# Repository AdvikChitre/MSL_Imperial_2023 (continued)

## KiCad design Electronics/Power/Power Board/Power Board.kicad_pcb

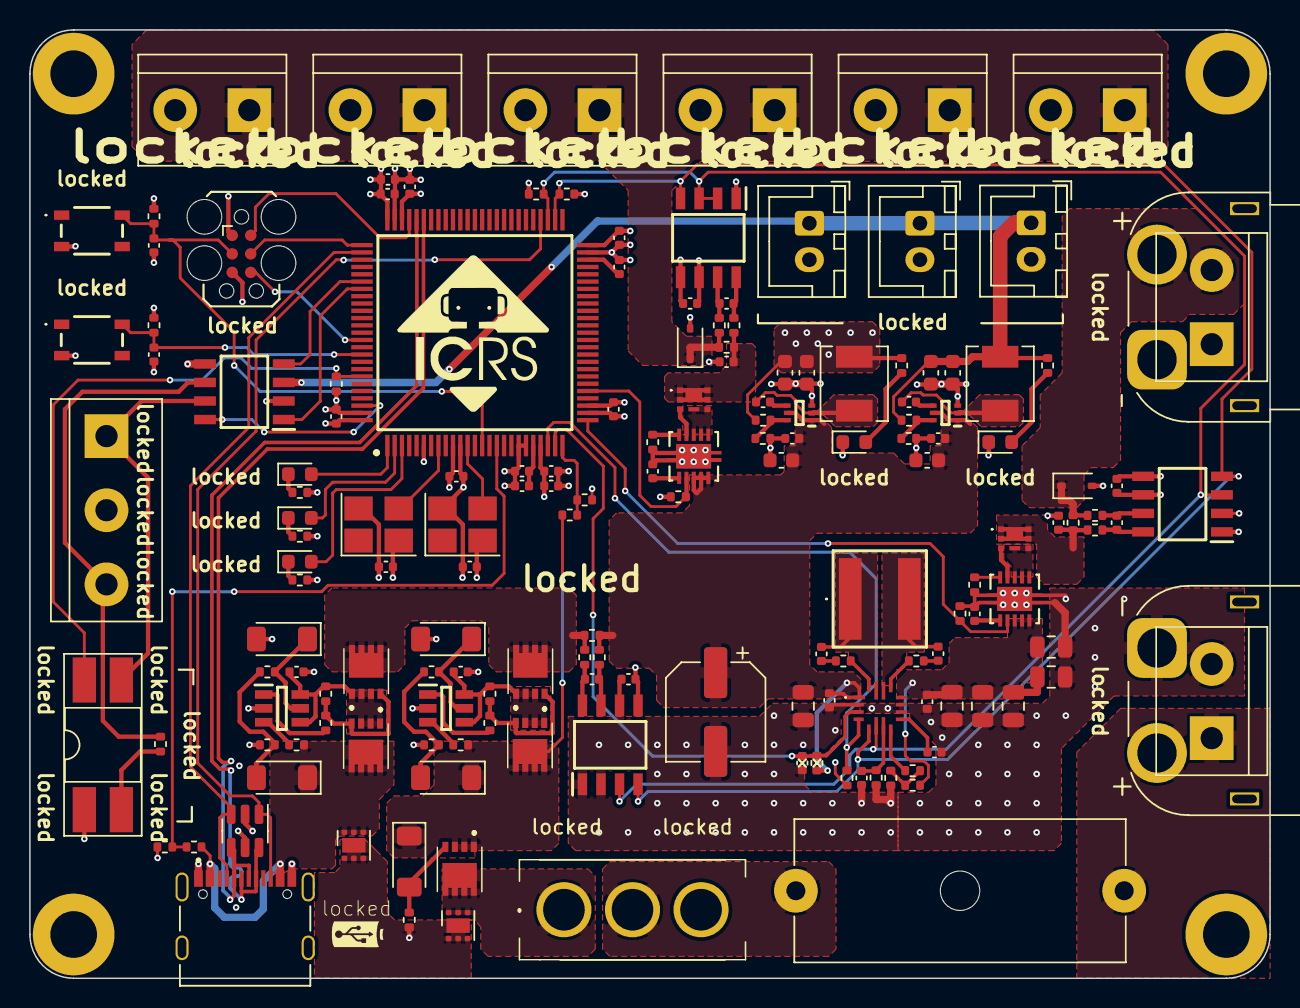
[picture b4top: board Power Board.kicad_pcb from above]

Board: 4 copper layers, 85.0 x 65.0 mm, 167 parts (0 on the bottom side), 94 nets.

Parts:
C201, C202, C205, C206, C209, C215, C216, C217, C218, C219, C220, C221, C235, C236, C301, C302, C305, C307, C310, C311, C312, C313, C314, C315: 100n; C_0402_1005Metric
C203, C211, C231, C237, C238, C306, C308: 1u; C_0402_1005Metric
C204, C233: 120p; C_0402_1005Metric
C207: 100u; CP_Elec_6.3x7.7
C208, C222, C223, C226, C227, C230: 22u; C_0805_2012Metric
C210, C212, C303, C304: 10n; C_0402_1005Metric
C213, C214, C224, C225, C228, C229: 22u; C_0603_1608Metric
C309: 4u7; C_0402_1005Metric
C316: 10u; C_0402_1005Metric
D201, D208: ZMM16V; D_MiniMELF
D202, D206: GREEN; LED_0603_1608Metric
D203, D209: ZMM4V7; D_MiniMELF
D204, D210: BAT760-115; D_SOD-323
D205: ZMM10V; D_MiniMELF
D301: Red; LED_0603_1608Metric
D302: Green; LED_0603_1608Metric
D303: Blue; LED_0603_1608Metric
F201: 10A; Fuseholder_Cylinder-5x20mm_Schurter_0031_8201_Horizontal_Op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
H101, H102, H103, H104: MountingHole_Pad; MountingHole_3.2mm_M3_DIN965_Pad
IC201, IC203, IC204: INA219AIDR; SOIC127P600X175-8N
IC202, IC208: TLV1805DBVR; SOT95P280X145-6N
IC205: MP28167GQ-A-Z; MP28167GQAZ
IC206, IC207: TPS563202DRLR; SOTFL50P160X60-6N
IC301: STM32U575VGT6; QFP50P1600X1600X160-100N
IC302: TJA1057GT/3; SOIC127P600X175-8N
J201: XT60PW-F; AMASS_XT60PW-F_1x02_P7.20mm_Horizontal
J202, J205, J206: JST-XH-2.50mm; JST_XH_B2B-XH-A_1x02_P2.50mm_Vertical
J203: XT60PW-M; AMASS_XT60PW-M_1x02_P7.20mm_Horizontal
J204, J215: Screw_Terminal_01x02; TerminalBlock_bornier-2_P5.08mm
J207, J208, J210, J211, J213, J214: Pluggable_Terminal_01x02; Pluggable_terminal-2_P5.08mm
J301: TC2030; Tag-Connect_TC2030-IDC-FP_2x03_P1.27mm_Vertical
J302: TYPE-C-31-M-12; HRO_TYPE-C-31-M-12
J303: Pluggable_Terminal_01x03; Pluggable_terminal-3_P5.08mm
L201: MPL-AL6050-4R7; MPLAL60504R7
L202: 4u7; L_Chilisin_BMRA00040420
L203: 3u3; L_Chilisin_BMRA00040420
Q201, Q202, Q203, Q204, Q205: DMP3013SFV-7; DMP3013SFV7
Q206, Q207: SSM6K513NU,LF; SSM6K513NULF
R201, R203, R211, R213, R215, R235, R236, R238: 22R; R_0402_1005Metric
R202, R214: 2m; R_0402_1005Metric
R204, R210, R231: 4k7; R_0402_1005Metric
R205, R212: 33k; R_0402_1005Metric
R206, R232, R311, R313: 1k; R_0402_1005Metric
R207, R208, R209, R217, R234: 100k; R_0402_1005Metric
R216, R225, R227, R230, R233, R302, R303, R304, R310, R312: 10k; R_0402_1005Metric
R218: 21k5; R_0402_1005Metric
R219: 787k; R_0402_1005Metric
R220, R221: 0R; R_0402_1005Metric
R222: 430k; R_0402_1005Metric
R223: 39k2; R_0402_1005Metric
R224: 52k; R_0402_1005Metric
R226: 31k; R_0402_1005Metric
R228, R305, R306: 2k2; R_0402_1005Metric
R229, R307, R308, R309: 1k5; R_0402_1005Metric
R237: 10m; R_0402_1005Metric
R301: 120R; R_0402_1005Metric
S301, S302: TS20-42-25-WT-160-SMT-TR; TS204225WT160SMTTRMSL
SW201: SW_SPDT; Toggle_switch
SW301: SW_DIP_x02; DIP-4_W8.89mm_SMDSocket_LongPads
U201: TCKE800NA_RF; WSON10B_TOS
U202: TCKE812NA_RF; WSON10B_TOS
U203, U303: TVS1800DRV; WSON-6-1EP_2x2mm_P0.65mm_EP1x1.6mm
U302: USBLC6-4SC6-ES; SOT-23-6
X301: 25MHz_Clock; Oscillator_SMD_Abracon_ASE-4Pin_3.2x2.5mm_HandSoldering
X302: 32.768kHz_Clock; Oscillator_SMD_Abracon_ASE-4Pin_3.2x2.5mm_HandSoldering

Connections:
12V_EN: C210.2, IC205.3 (EN), IC301.24 (PA1), R217.2
12V_OUT_EN: IC301.26 (PA3), R209.1, U202.2 (EN/UVLO)
+3.3V: C202.2, C206.2, C225.1, C229.1, C236.2, C301.1, C302.2, C307.1, C308.1, C310.1, C311.1, C312.1, C313.1, C314.1, C315.1, C316.1, IC201.2 (A0), IC201.5 (VS), IC203.5 (VS), IC204.5 (VS), IC301.6 (VBAT), IC301.11 (VDD_1), IC301.22 (VDDA), IC301.28 (VDD_2), IC301.50 (VDD_3), IC301.73 (VDDUSB), IC301.75 (VDD_4), IC301.100 (VDD_5), IC302.5 (VIO), J301.1 (VCC), L203.2, R216.1, R226.1, R229.1, R302.2, R303.2, R305.1, R306.1, SW301.1, U302.5 (VBUS), X301.4 (VDD), X302.4 (VDD)
+5V: C224.1, C228.1, IC302.3 (VCC), J202.1, J205.1, J206.1, L202.2, R224.1, R228.1
+12V: C221.1, C222.1, C223.1, C226.1, C227.1, C230.1, IC205.12 (OUT), R222.1, U202.3 (VIN), U202.4 (VIN), U202.5 (VIN)
/Control/CANH: IC302.7 (CANH), J303.1, SW301.3
/Control/CANL: IC302.6 (CANL), J303.3, R301.1
/Control/CAN_SW: R301.2, SW301.2
/Control/CC1: IC301.77 (PA15), J302.A5 (CC1), U302.3 (IO2)
/Control/CC2: IC301.54 (PB15), J302.B5 (CC2), U302.1 (IO1)
/Control/LEDB_K: D303.1 (K), R309.2
/Control/LEDG_K: D302.1 (K), R308.2
/Control/LEDR_K: D301.1 (K), R307.2
/Control/VCAP: C309.1, IC301.48 (VCAP)
/Control/VREF+: C305.1, C306.1, IC301.21 (VREF+)
/Power/3V3_BST: C220.1, IC207.4 (BST)
/Power/3V3_FB: IC207.6 (FB), R226.2, R227.1
/Power/3V3_LED_A: D206.2 (A), R229.2
/Power/3V3_SW: C220.2, IC207.2 (SW), L203.1
/Power/3V65: C211.2, IC205.9 (VCC)
/Power/5V_BST: C219.1, IC206.4 (BST)
/Power/5V_FB: IC206.6 (FB), R224.2, R225.1
/Power/5V_LED_A: D202.2 (A), R228.2
/Power/5V_SW: C219.2, IC206.2 (SW), L202.1
/Power/12V_FB: IC205.8 (FB), R219.1
/Power/12V_FB_MID: R219.2, R222.2, R223.1
/Power/12V_OUT: D204.1 (K), J201.2 (+), J215.2, R202.1, R203.1
/Power/12V_OUT_D: C237.1, Q207.1 (D), Q207.2 (D), Q207.5 (D), Q207.6 (D), Q207.7 (D), R201.1, R202.2
/Power/12V_OUT_DV/DT: C233.1, U202.1 (DV/DT)
/Power/12V_OUT_G: Q207.3 (G), U202.9 (EFET)
/Power/12V_OUT_ILIM: R212.1, U202.10 (ILIM)
/Power/12V_OUT_S: Q207.4 (S), Q207.8 (S), U202.6 (VOUT), U202.7 (VOUT), U202.8 (VOUT)
/Power/12V_SW1: C217.1, IC205.15 (SW1), L201.1
/Power/12V_SW2: C218.2, IC205.14 (SW2), L201.2
/Power/12V_VIN+: C201.1, IC201.8 (IN+), R201.2
/Power/12V_VIN-: C201.2, IC201.7 (IN-), R203.2
/Power/BST11: IC205.16 (BST1), R220.1
/Power/BST12: C217.2, R220.2
/Power/BST21: IC205.13 (BST2), R221.2
/Power/BST22: C218.1, R221.1
/Power/OC: C212.1, IC205.7 (OC), R218.1
/Power/RP_PMOS_G: D205.2 (A), Q205.4 (G), R210.1
/Power/VBAT_COMP-: IC202.3 (-), R230.2
/Power/VBAT_COMP_OUT: IC202.1, R211.1
/Power/VBAT_FUSED: F201.2, SW201.2 (B)
/Power/VBAT_GATE: Q201.4 (G), Q203.4 (G), R208.2, R211.2
/Power/VBAT_SHDN_A: D201.2 (A), R204.1, R206.1
/Power/VBAT_SHDN_K: D203.1 (K), IC202.5 (SH), R206.2
/Power/VBAT_SOURCE: C203.1, IC202.4 (+), IC202.6 (V+), Q201.1 (S_1), Q201.2 (S_2), Q201.3 (S_3), Q203.1 (S_1), Q203.2 (S_2), Q203.3 (S_3), R208.1
/Power/VBAT_SWITCHED: Q205.5 (D_1), Q205.6 (D_2), Q205.7 (D_3), Q205.8 (D_4), Q205.9 (D_5), SW201.1 (A), U203.4 (IN), U203.5 (IN), U203.6 (IN)
/Power/VBUS_COMP-: IC208.3 (-), R233.2
/Power/VBUS_COMP_OUT: IC208.1, R235.1
/Power/VBUS_GATE: Q202.4 (G), Q204.4 (G), R234.2, R235.2
/Power/VBUS_SHDN_A: D208.2 (A), R231.1, R232.1
/Power/VBUS_SHDN_K: D209.1 (K), IC208.5 (SH), R232.2
/Power/VBUS_SOURCE: C231.1, IC208.4 (+), IC208.6 (V+), Q202.1 (S_1), Q202.2 (S_2), Q202.3 (S_3), Q204.1 (S_1), Q204.2 (S_2), Q204.3 (S_3), R234.1
/Power/VDD_VIN+: C205.1, IC204.8 (IN+), R213.2
/Power/VDD_VIN-: C205.2, IC204.7 (IN-), R215.2
/Power/VOUT_D: C238.1, Q206.1 (D), Q206.2 (D), Q206.5 (D), Q206.6 (D), Q206.7 (D), R236.1, R237.2
/Power/VOUT_DV/DT: C204.1, U201.1 (DV/DT)
/Power/VOUT_G: Q206.3 (G), U201.9 (EFET)
/Power/VOUT_ILIM: R205.1, U201.10 (ILIM)
/Power/VOUT_S: Q206.4 (S), Q206.8 (S), U201.6 (VOUT), U201.7 (VOUT), U201.8 (VOUT)
/Power/VOUT_VIN+: C235.1, IC203.8 (IN+), R236.2
/Power/VOUT_VIN-: C235.2, IC203.7 (IN-), R238.2
ALT: IC205.4 (ALT), IC301.23 (PA0), R216.2
BOOT0: IC301.94 (PH3-BOOT0), R304.1, SW301.4
BTN: C303.1, IC301.91 (PB5), R302.1, S301.2 (NO_2)
CAN_RX: IC301.81 (PD0), IC302.4 (RXD)
CAN_TX: IC301.82 (PD1), IC302.1 (TXD)
GND: C202.1, C203.2, C204.2, C206.1, C207.2, C208.2, C209.1, C210.1, C211.1, C212.2, C213.2, C214.2, C215.2, C216.2, C221.2, C222.2, C223.2, C224.2, C225.2, C226.2, C227.2, C228.2, C229.2, C230.2, C231.2, C233.2, C236.1, C237.2, C238.2, C301.2, C302.1, C303.2, C304.2, C305.2, C306.2, C307.2, C308.2, C309.2, C310.2, C311.2, C312.2, C313.2, C314.2, C315.2, C316.2, D202.1 (K), D203.2 (A), D204.2 (A), D206.1 (K), D209.2 (A), D210.2 (A), IC201.1 (A1), IC201.6 (GND), IC202.2 (V-), IC203.1 (A1), IC203.6 (GND), IC204.1 (A1), IC204.2 (A0), IC204.6 (GND), IC205.2 (GND_1), IC205.10 (AGND), IC205.11 (GND_2), IC206.3 (GND), IC207.3 (GND), IC208.2 (V-), IC301.10 (VSS_1), IC301.19 (VSSA), IC301.20 (VREF-), IC301.27 (VSS_2), IC301.49 (VSS_3), IC301.74 (VSS_4), IC301.99 (VSS_5), IC302.2 (GND), J201.1 (-), J202.2, J203.1 (-), J204.2, J205.2, J206.2, J207.2, J208.2, J210.2, J211.2, J213.2, J214.2, J215.1, J301.5 (GND), J302.A1_B12 (GND), J302.B1_A12 (GND), J303.2, R204.2, R205.2, R207.2, R209.2, R210.2, R212.2, R218.2, R223.2, R225.2, R227.2, R231.2, R304.2, R307.1, R308.1, R309.1, R311.2, R313.2, S301.3 (COM_1), S302.3 (COM_1), U201.11 (GND), U202.11 (GND), U203.1 (GND), U203.2 (GND), U203.3 (GND), U203.7 (GND), U302.2 (GND), U303.1 (GND), U303.2 (GND), U303.3 (GND), U303.7 (GND), X301.2 (GND), X302.2 (GND)
LEDB: D303.2 (A), IC301.3 (PE4)
LEDG: D302.2 (A), IC301.1 (PE2)
LEDR: D301.2 (A), IC301.2 (PE3)
NRST: C304.1, IC301.14 (NRST), J301.3 (~RESET), R303.1, S302.2 (NO_2)
OSC25M: IC301.12 (PH0-OSC_IN), X301.3 (OUT)
OSC32K: IC301.8 (PC14-OSC32_IN), X302.3 (OUT)
SCL: IC201.4 (SCL), IC203.4 (SCL), IC204.4 (SCL), IC205.5 (SCL), IC301.52 (PB13), R305.2
SDA: IC201.3 (SDA), IC203.2 (A0), IC203.3 (SDA), IC204.3 (SDA), IC205.6 (SDA), IC301.53 (PB14), R306.2
SILENT: IC301.98 (PE1), IC302.8 (S)
SWCLK: IC301.76 (PA14), J301.4 (SWCLK)
SWDIO: IC301.72 (PA13), J301.2 (SWDIO)
SWO: IC301.89 (PB3), J301.6 (SWO)
USB_DN: IC301.70 (PA11), J302.A7 (DN1), J302.B7 (DN2), U302.4 (IO3)
USB_DP: IC301.71 (PA12), J302.A6 (DP1), J302.B6 (DP2), U302.6 (IO4)
VBAT: D201.1 (K), D205.1 (K), Q203.5 (D_1), Q203.6 (D_2), Q203.7 (D_3), Q203.8 (D_4), Q203.9 (D_5), Q205.1 (S_1), Q205.2 (S_2), Q205.3 (S_3), R230.1, R310.1
VBAT_RAW: F201.1, J203.2 (+), J204.1
VBAT/11: IC301.25 (PA2), R310.2, R311.1
VBUS: D208.1 (K), J302.A4_B9 (VBUS), J302.B4_A9 (VBUS), Q202.5 (D_1), Q202.6 (D_2), Q202.7 (D_3), Q202.8 (D_4), Q202.9 (D_5), R233.1, R312.1, U303.4 (IN), U303.5 (IN), U303.6 (IN)
VBUS/11: IC301.16 (PC1), R312.2, R313.1
VDD: C207.1, C208.1, C209.2, C213.1, C214.1, C215.1, C216.1, IC205.1 (IN), IC206.1 (VIN), IC206.5 (EN), IC207.1 (VIN), IC207.5 (EN), R214.1, R215.1, R217.1, U201.3 (VIN), U201.4 (VIN), U201.5 (VIN)
VIN: Q201.5 (D_1), Q201.6 (D_2), Q201.7 (D_3), Q201.8 (D_4), Q201.9 (D_5), Q204.5 (D_1), Q204.6 (D_2), Q204.7 (D_3), Q204.8 (D_4), Q204.9 (D_5), R213.1, R214.2
VOUT: D210.1 (K), J207.1, J208.1, J210.1, J211.1, J213.1, J214.1, R237.1, R238.1
VOUT_EN: IC301.30 (PA5), R207.1, U201.2 (EN/UVLO)

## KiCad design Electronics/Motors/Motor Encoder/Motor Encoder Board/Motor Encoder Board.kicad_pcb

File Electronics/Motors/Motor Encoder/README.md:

| Part | Function | Price/unit | Quantity | Link |
| - | - | - | - | - |
| AS5600-ASOT | Magnetic potentiometer | 0.98 | 1 | [LCSC](https://www.lcsc.com/product-detail/Position-Sensor_AMS-AS5600-ASOT_C499458.html)

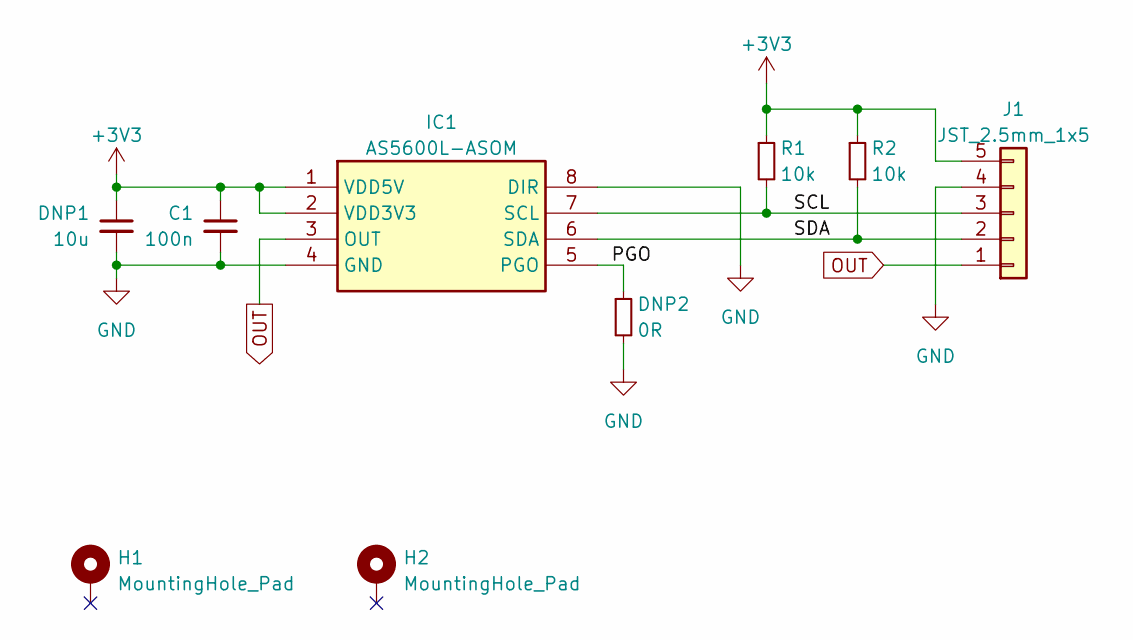
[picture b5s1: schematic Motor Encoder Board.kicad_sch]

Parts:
C1: 100n; C_0402_1005Metric
DNP1: 10u; C_0402_1005Metric
DNP2: 0R; R_0402_1005Metric
H1, H2: MountingHole_Pad; MountingHole_3.2mm_M3_DIN965_Pad
IC1: AS5600L-ASOM; SOIC127P600X175-8N; Mouser Part Number 985-AS5600L-ASOM
J1: JST_2.5mm_1x5; JST_XH_B5B-XH-A_1x05_P2.50mm_Vertical
R1, R2: 10k; R_0402_1005Metric

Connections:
+3V3: C1.1, DNP1.1, IC1.1 (VDD5V), IC1.2 (VDD3V3), J1.5, R1.1, R2.1
/PGO: DNP2.1, IC1.5 (PGO)
/SCL: IC1.7 (SCL), J1.3, R1.2
/SDA: IC1.6 (SDA), J1.2, R2.2
GND: C1.2, DNP1.2, DNP2.2, IC1.4 (GND), IC1.8 (DIR), J1.4
OUT: IC1.3 (OUT), J1.1

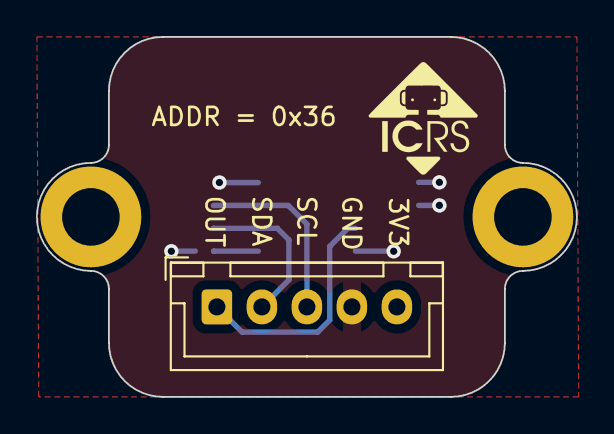
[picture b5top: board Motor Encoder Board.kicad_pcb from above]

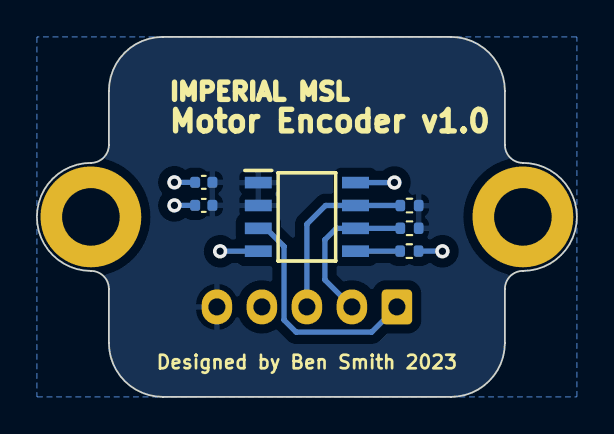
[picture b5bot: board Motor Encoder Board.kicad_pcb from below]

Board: 2 copper layers, 30.0 x 20.0 mm, 9 parts (6 on the bottom side), 6 nets.

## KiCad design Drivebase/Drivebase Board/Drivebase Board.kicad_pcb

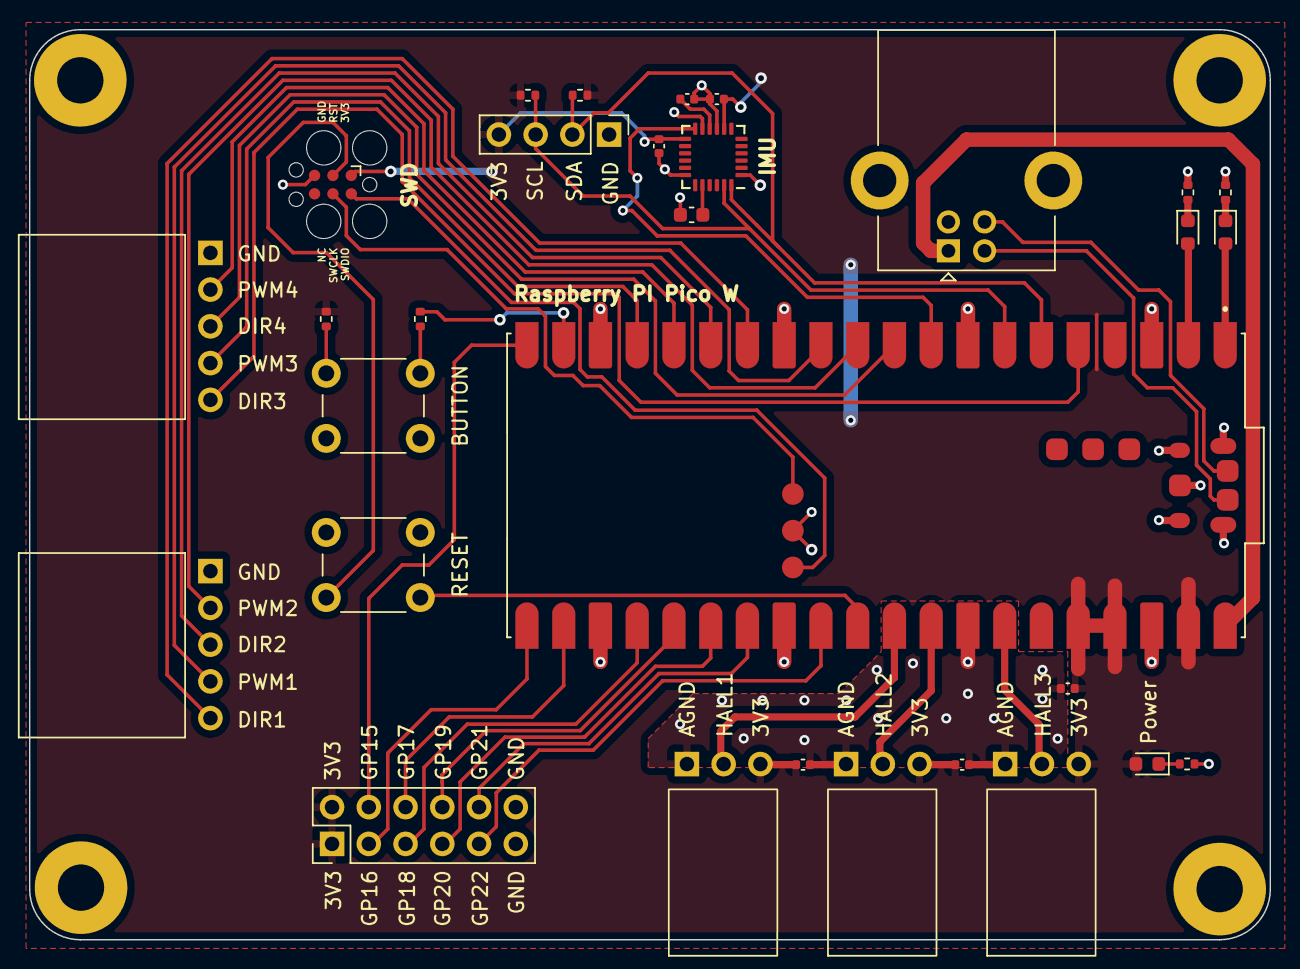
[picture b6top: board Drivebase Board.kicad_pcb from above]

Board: 2 copper layers, 85.8 x 62.9 mm, 37 parts (0 on the bottom side), 40 nets.

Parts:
C101, C102, C103, C104, C106: 100n; C_0402_1005Metric
C105: 2n2; C_0603_1608Metric
C107: 10n; C_0402_1005Metric
D101, D102, D103: LED_Small; LED_0603_1608Metric
H101, H102, H103, H104: MountingHole; MountingHole_3.2mm_M3_Pad
J101, J102: Conn_01x05_Male; 5pin right angle header
J103, J104, J105: Conn_01x03_Male; 3pin right angle header
J106: TC2030-IDC; Tag-Connect_TC2030-IDC-FP_2x03_P1.27mm_Vertical
J107: Conn_01x04_Male; PinHeader_1x04_P2.54mm_Vertical
J108: USB_A; USB_B_Lumberg_2411_02_Horizontal
J109: Conn_02x06_Odd_Even; PinHeader_2x06_P2.54mm_Vertical
R101, R102: 4k7; R_0402_1005Metric
R103, R105, R106, R107: 330R; R_0402_1005Metric
R104: 100k; R_0402_1005Metric
SW101, SW102: PSH_BTN; SW_PUSH_6mm_H5mm
TP101, TP102, TP103: TestPoint; TestPoint_Pad_D1.5mm
U101: SC0915; MODULE_SC0915
U102: MPU-6050; InvenSense_QFN-24_4x4mm_P0.5mm

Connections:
+3V3: C101.1, C102.1, C103.1, C106.1, C107.1, D101.2 (A), J103.3, J104.3, J105.3, J106.1, J107.4, J109.1, J109.2, R101.1, R102.1, R104.2, U101.36 (3V3_OUT), U101.37 (3V3_EN), U101.39 (VSYS), U102.8 (VDDIO), U102.13 (VDD)
/IMU_CPOUT: C105.1, U102.20 (CPOUT)
/IMU_REGOUT: C104.1, U102.10 (REGOUT)
/LED1_K: D102.1 (K), R106.1
/LED2_K: D103.1 (K), R107.1
/LED_PWR_K: D101.1 (K), R105.1
BTN: R103.2, U101.19 (GP14)
DIR1: J102.5, U101.14 (GP10)
DIR2: J102.3, U101.15 (GP11)
DIR3: J101.5, U101.5 (GP3)
DIR4: J101.3, U101.10 (GP7)
DM: J108.2 (D-), U101.TP2 (TP2_USB_DM)
DP: J108.3 (D+), U101.TP3 (TP3_USB_DP)
GND: C104.2, C105.2, C106.2, C107.2, J101.1, J102.1, J106.5, J107.1, J108.4 (GND), J108.5 (Shield), J109.11, J109.12, R105.2, R106.2, R107.2, SW101.1, SW102.2, TP103.1, U101.3 (GND), U101.8 (GND), U101.13 (GND), U101.18 (GND), U101.23 (GND), U101.28 (GND), U101.38 (GND), U101.A (USB_SHIELD), U101.B (USB_SHIELD), U101.C (USB_SHIELD), U101.D (USB_SHIELD), U101.TP1 (TP1_GND), U102.1 (CLKIN), U102.9 (AD0), U102.11 (FSYNC), U102.18 (GND)
GNDA: C101.2, C102.2, C103.2, J103.1, J104.1, J105.1, U101.33 (AGND)
GPIO15: J109.4, U101.20 (GP15)
GPIO16: J109.3, U101.21 (GP16)
GPIO17: J109.6, U101.22 (GP17)
GPIO18: J109.5, U101.24 (GP18)
GPIO19: J109.8, U101.25 (GP19)
GPIO20: J109.7, U101.26 (GP20)
GPIO21: J109.10, U101.27 (GP21)
GPIO22: J109.9, U101.29 (GP22)
HALL1: J103.2, U101.31 (GP26)
HALL2: J104.2, U101.32 (GP27)
HALL3: J105.2, U101.34 (GP28)
IMU_INT: U101.9 (GP6), U102.12 (INT)
LED1: D102.2 (A), U101.1 (GP0)
LED2: D103.2 (A), U101.2 (GP1)
unnamed: R103.1, R104.1, SW101.2
PWM1: J102.4, U101.12 (GP9)
PWM2: J102.2, U101.11 (GP8)
PWM3: J101.4, U101.17 (GP13)
PWM4: J101.2, U101.16 (GP12)
RST: J106.3, SW102.1, U101.30 (~RUN)
SCL: J107.3, R102.2, U101.7 (GP5), U102.23 (SCL)
SDA: J107.2, R101.2, U101.6 (GP4), U102.24 (SDA)
SWCLK: J106.4, TP101.1
SWDIO: J106.2, TP102.1
VBUS: J108.1 (VBUS), U101.40 (VBUS)

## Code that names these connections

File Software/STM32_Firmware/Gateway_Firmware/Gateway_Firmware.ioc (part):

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Mcu.Name=STM32H723ZGTx
Mcu.Package=LQFP144
Mcu.UserName=STM32H723ZGTx
PA1.Mode=RMII
PA1.Signal=ETH_REF_CLK
PA11.Mode=Device_Only_FS
PA11.Signal=USB_OTG_HS_DM
PA12.Mode=Device_Only_FS
PA12.Signal=USB_OTG_HS_DP
PA13(JTMS/SWDIO).Mode=Trace_Asynchronous_SW
PA13(JTMS/SWDIO).Signal=DEBUG_JTMS-SWDIO
PA14(JTCK/SWCLK).Mode=Trace_Asynchronous_SW
PA14(JTCK/SWCLK).Signal=DEBUG_JTCK-SWCLK
PA2.Mode=RMII
PA2.Signal=ETH_MDIO
PA7.Mode=RMII
PA7.Signal=ETH_CRS_DV
PA8.GPIOParameters=GPIO_Label
PA8.GPIO_Label=SDMMC1_CD
PA8.Signal=GPIO_Input
PB11.Mode=RMII
PB11.Signal=ETH_TX_EN
PB12.Mode=RMII
PB12.Signal=ETH_TXD0
PB13.Mode=RMII
PB13.Signal=ETH_TXD1
PB3(JTDO/TRACESWO).Mode=Trace_Asynchronous_SW
PB3(JTDO/TRACESWO).Signal=DEBUG_JTDO-SWO
PB5.Mode=FDCAN_Activate
PB5.Signal=FDCAN2_RX
PB6.Mode=FDCAN_Activate
PB6.Signal=FDCAN2_TX
PC1.Mode=RMII
PC1.Signal=ETH_MDC
PC10.Mode=SD_4_bits_Wide_bus
PC10.Signal=SDMMC1_D2
PC11.Mode=SD_4_bits_Wide_bus
PC11.Signal=SDMMC1_D3
PC12.Mode=SD_4_bits_Wide_bus
PC12.Signal=SDMMC1_CK
PC14-OSC32_IN.Mode=LSE-External-Clock-Source
PC14-OSC32_IN.Signal=RCC_OSC32_IN
PC4.Mode=RMII
PC4.Signal=ETH_RXD0
PC5.Mode=RMII
PC5.Signal=ETH_RXD1
PC8.Mode=SD_4_bits_Wide_bus
PC8.Signal=SDMMC1_D0
PC9.Mode=SD_4_bits_Wide_bus
PC9.Signal=SDMMC1_D1
PD0.Mode=FDCAN_Activate
PD0.Signal=FDCAN1_RX
PD1.Mode=FDCAN_Activate
PD1.Signal=FDCAN1_TX
PD2.Mode=SD_4_bits_Wide_bus
PD2.Signal=SDMMC1_CMD
PF6.Mode=FDCAN_Activate
PF6.Signal=FDCAN3_RX
PF7.Mode=FDCAN_Activate
PF7.Signal=FDCAN3_TX
PH0-OSC_IN.Mode=HSE-External-Clock-Source
PH0-OSC_IN.Signal=RCC_OSC_IN
RCC.SYSCLKFreq_VALUE=550000000
RCC.SYSCLKSource=RCC_SYSCLKSOURCE_PLLCLK
board=custom

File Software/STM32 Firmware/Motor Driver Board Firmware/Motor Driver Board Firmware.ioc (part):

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Mcu.Name=STM32H723ZGTx
Mcu.Package=LQFP144
Mcu.UserName=STM32H723ZGTx
PA0.Signal=S_TIM2_CH1_ETR
PA1.Signal=S_TIM2_CH2
PA11.Mode=Device_Only_FS
PA11.Signal=USB_OTG_HS_DM
PA12.Mode=Device_Only_FS
PA12.Signal=USB_OTG_HS_DP
PA13(JTMS/SWDIO).Mode=Trace_Asynchronous_SW
PA13(JTMS/SWDIO).Signal=DEBUG_JTMS-SWDIO
PA14(JTCK/SWCLK).Mode=Trace_Asynchronous_SW
PA14(JTCK/SWCLK).Signal=DEBUG_JTCK-SWCLK
PA4.Signal=COMP_DAC11_group
PA6.Signal=ADCx_INP3
PA8.Mode=I2C
PA8.Signal=I2C3_SCL
PB0.Signal=ADCx_INP9
PB10.Mode=I2C
PB10.Signal=I2C2_SCL
PB11.Mode=I2C
PB11.Signal=I2C2_SDA
PB12.Signal=GPIO_Input
PB13.Signal=GPIO_Input
PB14.Signal=S_TIM12_CH1
PB15.Signal=S_TIM12_CH2
PB3(JTDO/TRACESWO).Mode=Trace_Asynchronous_SW
PB3(JTDO/TRACESWO).Signal=DEBUG_JTDO-SWO
PC14-OSC32_IN.Mode=LSE-External-Clock-Source
PC14-OSC32_IN.Signal=RCC_OSC32_IN
PC9.Mode=I2C
PC9.Signal=I2C3_SDA
PD0.Mode=FDCAN_Activate
PD0.Signal=FDCAN1_RX
PD1.Mode=FDCAN_Activate
PD1.Signal=FDCAN1_TX
PD10.Signal=GPIO_Input
PD8.Signal=GPIO_Output
PD9.Signal=GPIO_Input
PE11.Signal=S_TIM1_CH2
PE12.Mode=Full_Duplex_Master
PE12.Signal=SPI4_SCK
PE13.Mode=Full_Duplex_Master
PE13.Signal=SPI4_MISO
PE14.Mode=Full_Duplex_Master
PE14.Signal=SPI4_MOSI
PE4.Mode=NSS_Signal_Hard_Output
PE4.Signal=SPI4_NSS
PE9.Signal=S_TIM1_CH1
PF11.Mode=IN2-Single-Ended
PF11.Signal=ADC1_INP2
PF14.Mode=I2C
PF14.Signal=I2C4_SCL
PF15.Mode=I2C
PF15.Signal=I2C4_SDA
PH0-OSC_IN.Mode=HSE-External-Clock-Source
PH0-OSC_IN.Signal=RCC_OSC_IN
RCC.SYSCLKFreq_VALUE=550000000
RCC.SYSCLKSource=RCC_SYSCLKSOURCE_PLLCLK
board=custom

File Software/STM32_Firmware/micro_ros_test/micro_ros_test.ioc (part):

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Mcu.Name=STM32H723ZGTx
Mcu.Package=LQFP144
Mcu.UserName=STM32H723ZGTx
PA1.GPIOParameters=GPIO_Speed,GPIO_PuPd,GPIO_Mode
PA1.GPIO_Mode=GPIO_MODE_AF_PP
PA1.GPIO_PuPd=GPIO_NOPULL
PA1.GPIO_Speed=GPIO_SPEED_FREQ_LOW
PA1.Mode=RMII
PA1.Signal=ETH_REF_CLK
PA10.GPIOParameters=GPIO_Label
PA10.GPIO_Label=USB_FS_ID
PA10.Mode=OTG/Dual-Role-Device-FS
PA10.Signal=USB_OTG_HS_ID
PA11.GPIOParameters=GPIO_Label
PA11.GPIO_Label=USB_FS_DM
PA11.Mode=OTG/Dual-Role-Device-FS
PA11.Signal=USB_OTG_HS_DM
PA12.GPIOParameters=GPIO_Label
PA12.GPIO_Label=USB_FS_DP
PA12.Mode=OTG/Dual-Role-Device-FS
PA12.Signal=USB_OTG_HS_DP
PA13(JTMS/SWDIO).GPIOParameters=GPIO_Label
PA13(JTMS/SWDIO).GPIO_Label=SWDIO
PA13(JTMS/SWDIO).Mode=Trace_Asynchronous_SW
PA13(JTMS/SWDIO).Signal=DEBUG_JTMS-SWDIO
PA14(JTCK/SWCLK).GPIOParameters=GPIO_Label
PA14(JTCK/SWCLK).GPIO_Label=SWCLK
PA14(JTCK/SWCLK).Mode=Trace_Asynchronous_SW
PA14(JTCK/SWCLK).Signal=DEBUG_JTCK-SWCLK
PA2.GPIOParameters=GPIO_Speed,GPIO_PuPd,GPIO_Mode
PA2.GPIO_Mode=GPIO_MODE_AF_PP
PA2.GPIO_PuPd=GPIO_NOPULL
PA2.GPIO_Speed=GPIO_SPEED_FREQ_LOW
PA2.Mode=RMII
PA2.Signal=ETH_MDIO
PA7.GPIOParameters=GPIO_Speed,GPIO_PuPd,GPIO_Mode
PA7.GPIO_Mode=GPIO_MODE_AF_PP
PA7.GPIO_PuPd=GPIO_NOPULL
PA7.GPIO_Speed=GPIO_SPEED_FREQ_LOW
PA7.Mode=RMII
PA7.Signal=ETH_CRS_DV
PA9.GPIOParameters=GPIO_Label
PA9.GPIO_Label=USB_FS_VBUS
PA9.Mode=Activate_VBUS_FS
PA9.Signal=USB_OTG_HS_VBUS
PB0.GPIOParameters=GPIO_Label
PB0.GPIO_Label=LED_GREEN
PB0.Signal=GPIO_Output
PB13.GPIOParameters=GPIO_Speed,GPIO_PuPd,GPIO_Mode
PB13.GPIO_Mode=GPIO_MODE_AF_PP
PB13.GPIO_PuPd=GPIO_NOPULL
PB13.GPIO_Speed=GPIO_SPEED_FREQ_LOW
PB13.Mode=RMII
PB13.Signal=ETH_TXD1
PB14.GPIOParameters=GPIO_Label
PB14.GPIO_Label=LED_RED
PB14.Signal=GPIO_Output
PB3(JTDO/TRACESWO).GPIOParameters=GPIO_Label
PB3(JTDO/TRACESWO).GPIO_Label=SWO
PB3(JTDO/TRACESWO).Mode=Trace_Asynchronous_SW
PB3(JTDO/TRACESWO).Signal=DEBUG_JTDO-SWO
PC1.GPIOParameters=GPIO_Speed,GPIO_PuPd,GPIO_Mode
PC1.GPIO_Mode=GPIO_MODE_AF_PP
PC1.GPIO_PuPd=GPIO_NOPULL
PC1.GPIO_Speed=GPIO_SPEED_FREQ_LOW
PC1.Mode=RMII
PC1.Signal=ETH_MDC
PC13.GPIOParameters=GPIO_Label
PC13.GPIO_Label=B1 (Blue_User_Button)
PC13.Signal=GPIO_Input
PC14-OSC32_IN.Mode=LSE-External-Oscillator
PC14-OSC32_IN.Signal=RCC_OSC32_IN
PC15-OSC32_OUT.Mode=LSE-External-Oscillator
PC15-OSC32_OUT.Signal=RCC_OSC32_OUT
PC4.GPIOParameters=GPIO_Speed,GPIO_PuPd,GPIO_Mode
PC4.GPIO_Mode=GPIO_MODE_AF_PP
PC4.GPIO_PuPd=GPIO_NOPULL
PC4.GPIO_Speed=GPIO_SPEED_FREQ_LOW
PC4.Mode=RMII
PC4.Signal=ETH_RXD0
PC5.GPIOParameters=GPIO_Speed,GPIO_PuPd,GPIO_Mode
PC5.GPIO_Mode=GPIO_MODE_AF_PP
PC5.GPIO_PuPd=GPIO_NOPULL
PC5.GPIO_Speed=GPIO_SPEED_FREQ_LOW
PC5.Mode=RMII
PC5.Signal=ETH_RXD1
PD10.GPIOParameters=GPIO_Label
PD10.GPIO_Label=USB_FS_PWR_EN
PD10.Signal=GPIO_Output
PD8.GPIOParameters=GPIO_Label
PD8.GPIO_Label=STLK_VCP_RX
PD8.Mode=Asynchronous
PD8.Signal=USART3_TX
PD9.GPIOParameters=GPIO_Label
PD9.GPIO_Label=STLK_VCP_TX
PD9.Mode=Asynchronous
PD9.Signal=USART3_RX
PE1.GPIOParameters=GPIO_Label
PE1.GPIO_Label=LED_YELLOW
PE1.Signal=GPIO_Output
PG11.GPIOParameters=GPIO_Speed,GPIO_PuPd,GPIO_Mode
PG11.GPIO_Mode=GPIO_MODE_AF_PP
PG11.GPIO_PuPd=GPIO_NOPULL
PG11.GPIO_Speed=GPIO_SPEED_FREQ_LOW
PG11.Mode=RMII
PG11.Signal=ETH_TX_EN
PG13.GPIOParameters=GPIO_Speed,GPIO_PuPd,GPIO_Mode
PG13.GPIO_Mode=GPIO_MODE_AF_PP
PG13.GPIO_PuPd=GPIO_NOPULL
PG13.GPIO_Speed=GPIO_SPEED_FREQ_LOW
PG13.Mode=RMII
PG13.Signal=ETH_TXD0
PG7.GPIOParameters=GPIO_Label
PG7.GPIO_Label=USB_FS_OVCR
PG7.Signal=GPXTI7
PH0-OSC_IN.GPIOParameters=GPIO_Label
PH0-OSC_IN.GPIO_Label=MCO
PH0-OSC_IN.Mode=HSE-External-Clock-Source
PH0-OSC_IN.Signal=RCC_OSC_IN
PH1-OSC_OUT.Signal=RCC_OSC_OUT
RCC.HSE_VALUE=8000000
RCC.SYSCLKFreq_VALUE=550000000
RCC.SYSCLKSource=RCC_SYSCLKSOURCE_PLLCLK
board=NUCLEO-H723ZG
boardIOC=true

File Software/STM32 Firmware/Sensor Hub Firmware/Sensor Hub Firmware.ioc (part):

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Mcu.Name=STM32H723ZGTx
Mcu.Package=LQFP144
Mcu.UserName=STM32H723ZGTx
PA11.Mode=Device_Only_FS
PA11.Signal=USB_OTG_HS_DM
PA12.Mode=Device_Only_FS
PA12.Signal=USB_OTG_HS_DP
PA13(JTMS/SWDIO).Mode=Trace_Asynchronous_SW
PA13(JTMS/SWDIO).Signal=DEBUG_JTMS-SWDIO
PA14(JTCK/SWCLK).Mode=Trace_Asynchronous_SW
PA14(JTCK/SWCLK).Signal=DEBUG_JTCK-SWCLK
PA8.Mode=I2C
PA8.Signal=I2C3_SCL
PB3(JTDO/TRACESWO).Mode=Trace_Asynchronous_SW
PB3(JTDO/TRACESWO).Signal=DEBUG_JTDO-SWO
PB6.Mode=I2C
PB6.Signal=I2C1_SCL
PB7.Mode=I2C
PB7.Signal=I2C1_SDA
PC14-OSC32_IN.Mode=LSE-External-Clock-Source
PC14-OSC32_IN.Signal=RCC_OSC32_IN
PC9.Mode=I2C
PC9.Signal=I2C3_SDA
PD0.Mode=FDCAN_Activate
PD0.Signal=FDCAN1_RX
PD1.Mode=FDCAN_Activate
PD1.Signal=FDCAN1_TX
PE2.Mode=Full_Duplex_Master
PE2.Signal=SPI4_SCK
PE4.Mode=NSS_Signal_Hard_Output
PE4.Signal=SPI4_NSS
PE5.Mode=Full_Duplex_Master
PE5.Signal=SPI4_MISO
PE6.Mode=Full_Duplex_Master
PE6.Signal=SPI4_MOSI
PF14.Mode=I2C
PF14.Signal=I2C4_SCL
PF15.Mode=I2C
PF15.Signal=I2C4_SDA
PF6.Mode=NSS_Signal_Hard_Output
PF6.Signal=SPI5_NSS
PF7.Mode=Full_Duplex_Master
PF7.Signal=SPI5_SCK
PF8.Mode=Full_Duplex_Master
PF8.Signal=SPI5_MISO
PF9.Mode=Full_Duplex_Master
PF9.Signal=SPI5_MOSI
PH0-OSC_IN.Mode=HSE-External-Clock-Source
PH0-OSC_IN.Signal=RCC_OSC_IN
RCC.SYSCLKFreq_VALUE=550000000
RCC.SYSCLKSource=RCC_SYSCLKSOURCE_PLLCLK
board=custom

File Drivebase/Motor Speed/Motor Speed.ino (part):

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#define PWM3 13
#define PWM4 12

#define DIR1 10
#define DIR2 11
#define DIR3 3
#define DIR4 7

#define HALL1 A0
#define HALL2 A1
#define HALL3 A2

#define BTN 14

#define LED1 0
#define LED2 1

#define IMU_INT 6
#define IMU_SCL 5
#define IMU_SDA 4

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static const uint16_t samples = 64;                                    // Number of samples collected before processing
static const uint16_t samplingFrequency = 1000;                        // Sampling frequency in Hz, default: 1000
static const uint8_t numberOfMotors = 3;                               // Number of motors, default: 3
static const int8_t motors[numberOfMotors] = { HALL1, HALL2, HALL3 };  // Vector to store the pins to sample for each motor
static const float thresholdStandardDeviation = 30;                    // Threshold in standard deviation to distinguish between noise and a signal

static volatile uint16_t sampleNumber = 0;          // Variable to store current sample number
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// Sample queue
static QueueHandle_t sampleQueue;

static const int8_t leds[3] = { LED_BUILTIN, LED1, LED2 };
static volatile bool ledStatus[3] = { false, false, false };

static const char startCharacter = '!';
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  (void)pvParameters;

  // Set input pins
  pinMode(HALL1, INPUT);
  pinMode(HALL2, INPUT);
  pinMode(HALL3, INPUT);

  // Create local variables
  uint16_t currentSample;
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
  // Set pins
  pinMode(LED_BUILTIN, OUTPUT);
  pinMode(LED1, OUTPUT);
  pinMode(LED2, OUTPUT);

  // Main loop
  while (true) {
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
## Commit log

2023-02-01 Added serial python script and info spreadsheet
2023-02-01 Second commit, added arduino code for drive base stuff
2023-02-01 Improved the function that gets the motor frequency
2023-02-02 Added PCB files and removed old files
2023-02-03 Added a queue for the ADC samples
2023-02-04 Still bugged - weird stuff with print statements
2023-02-04 Oops I wrote the message in a different change
2023-02-08 Fixed bug: FreeRTOS queue used before its creation
2023-02-08 Minor bug fixes, still broken
2023-02-08 Python script to test serial_send
2023-02-08 Still broken: serial write gets stuck in infinite loop?
2023-02-10 Fixed task that gets motor frequency
2023-02-10 Created archive of old code in case its needed
2023-02-10 Updated with current information (still needs work)
2023-02-10 Minor changes to led function
2023-02-10 Library files incomplete so pulled for time being
2023-02-11 Added rolling average of measured frequencies
2023-02-11 Updated to .cpp file type
2023-02-11 Moved archived code file
2023-02-11 Added PID controller, still needs tuning
2023-02-12 PID control loop mostly implemented
2023-02-12 PID Controller mostly works, I need to sleep
2023-02-16 Updated archived code
2023-02-16 Need to add FIR filter to measured frequencies
2023-02-16 Added FIR filter
2023-02-17 Finished control! :) Need to tune PID better though
2023-02-19 J-Link debugger setup
2023-02-19 Added IMU code to get orientation
2023-02-27 object detector + decision tree
2023-02-27 Added control scheme diagram
2023-02-27 Fianl code for test video
2023-02-27 No change
2023-06-27 Tidied up
2023-06-28 Tidying + motor encoder PCB
2023-06-29 Created power board and firmware projects
2023-06-30 Motor driver + power board progress
2023-07-01 PCB Schematic progress
2023-07-01 Updated gitignore
2023-07-01 PCB Schematics finished
2023-07-07 Schematic updates
2023-07-10 PCB layout progress, spice simulations for power board
2023-07-10 Implemented power supply selector
2023-07-10 Finished power board layout
2023-07-12 Gateway board layout complete and routing begun
2023-07-14 Sensor hub board done
2023-07-15 Motor driver and power boards done
2023-07-17 All boards done
2023-07-17 Added CANopenEditor submodule
2023-07-17 Added "ibom"s for PCBs
2023-07-18 Bug fixes
2023-07-18 Renamed folders and added software README.md
2023-07-23 Tidied, added STM32 ethernet example, minor PCB changes
2023-07-23 Updated .gitignore
2023-07-24 Tided up, new firmware projects, microros setup
